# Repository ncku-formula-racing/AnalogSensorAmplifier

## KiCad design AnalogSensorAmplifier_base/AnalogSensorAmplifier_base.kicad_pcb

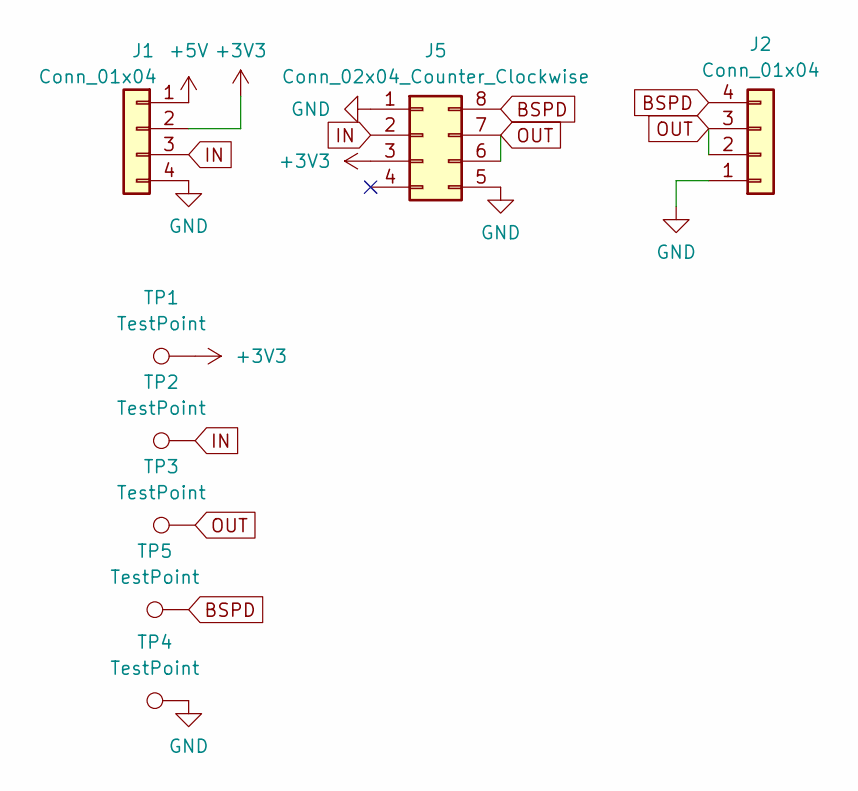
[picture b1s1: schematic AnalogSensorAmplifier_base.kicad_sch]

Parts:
J1, J2: Conn_01x04; PinHeader_1x04_P2.54mm_Vertical
J5: Conn_02x04_Counter_Clockwise; AnalogSensorAmplifier
TP1, TP2, TP3, TP4, TP5: TestPoint; TestPoint_THTPad_D1.0mm_Drill0.5mm

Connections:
+3V3: J1.2, J5.3, TP1.1
+5V: J1.1
BSPD: J2.4, J5.8, TP5.1
GND: J1.4, J2.1, J5.1, J5.5, TP4.1
IN: J1.3, J5.2, TP2.1
OUT: J2.2, J2.3, J5.6, J5.7, TP3.1

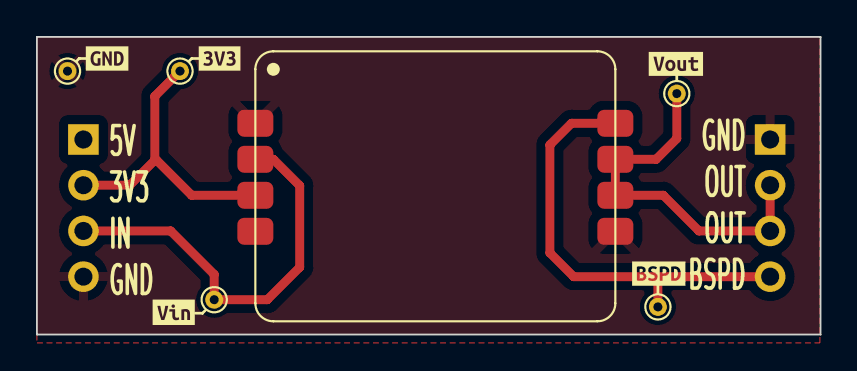
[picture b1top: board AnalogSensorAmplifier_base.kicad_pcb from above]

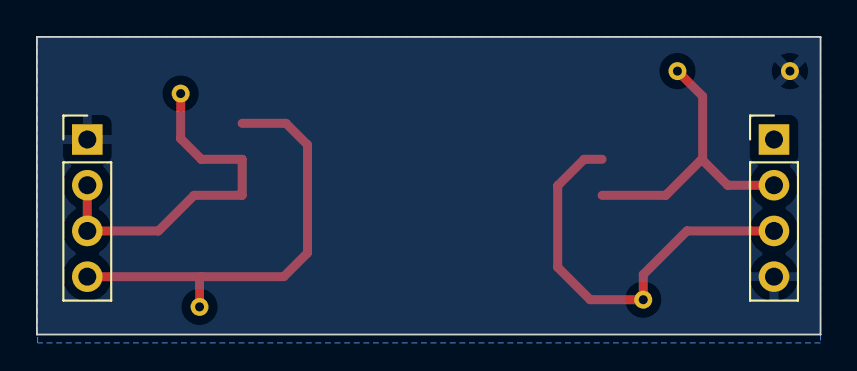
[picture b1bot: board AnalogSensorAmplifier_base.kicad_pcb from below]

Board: 2 copper layers, 43.5 x 16.5 mm, 13 parts (2 on the bottom side), 5 nets.

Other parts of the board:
kibuzzard-6607C7C2: G***; kibuzzard-6607C7C2
kibuzzard-6607C7E7: G***; kibuzzard-6607C7E7
kibuzzard-6607C702: G***; kibuzzard-6607C702
kibuzzard-6607C735: G***; kibuzzard-6607C735
kibuzzard-6607C802: G***; kibuzzard-6607C802

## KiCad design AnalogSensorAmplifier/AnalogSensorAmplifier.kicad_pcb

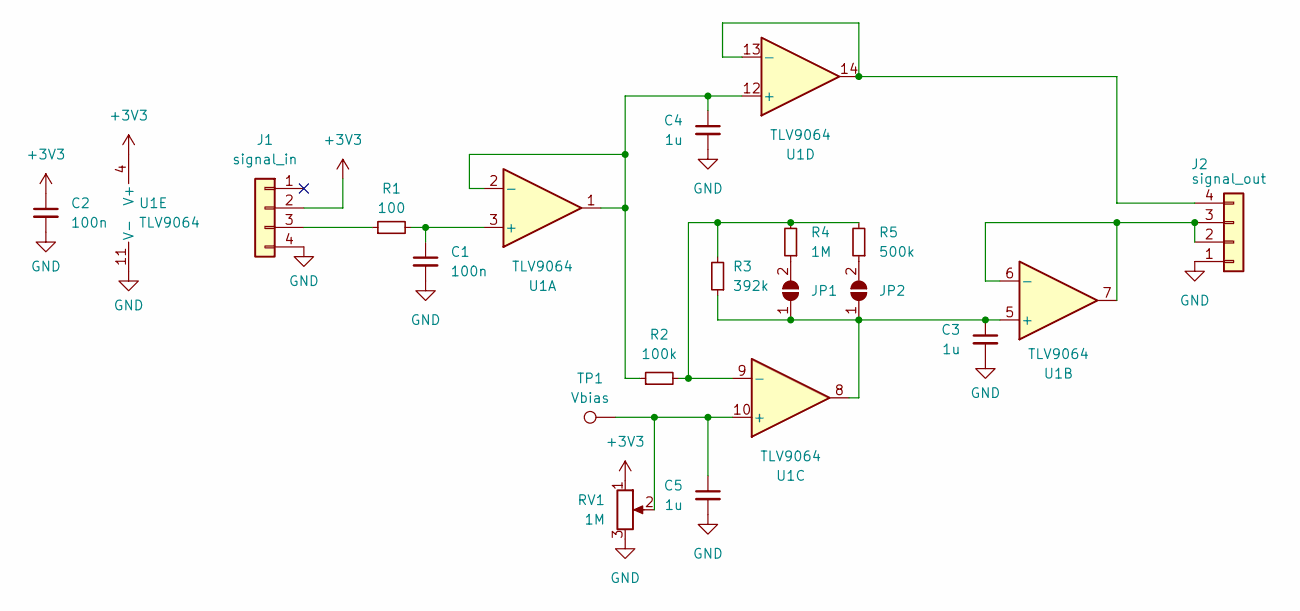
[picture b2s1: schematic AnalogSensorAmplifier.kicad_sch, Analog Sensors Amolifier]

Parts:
C1, C2: 100n; C_0603_1608Metric
C3, C4, C5: 1u; C_0603_1608Metric
J1: signal_in; PinHeader_1x04_P2.00mm_Vertical
J2: signal_out; PinHeader_1x04_P2.00mm_Vertical
JP1, JP2: SolderJumper_2_Open; small jumper
R1: 100; R_0603_1608Metric
R2: 100k; R_0603_1608Metric
R3: 392k; R_0603_1608Metric
R4: 1M; R_0603_1608Metric
R5: 500k; R_0603_1608Metric
RV1: 1M; PVG3A
TP1: Vbias; TestPoint_THTPad_D1.0mm_Drill0.5mm
U1: TLV9064; SOIC-14_3.9x8.7mm_P1.27mm

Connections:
+3V3: C2.1, J1.2, RV1.1, U1.4 (V+)
GND: C1.2, C2.2, C3.2, C4.2, C5.2, J1.4, J2.1, RV1.3, U1.11 (V-)
unnamed: J1.3, R1.1
unnamed: J2.2, J2.3, U1.6 (-), U1.7
unnamed: J2.4, U1.13 (-), U1.14
unnamed: C3.1, JP1.1 (A), JP2.1 (A), R3.1, U1.5 (+), U1.8
unnamed: JP1.2 (B), R4.1
unnamed: JP2.2 (B), R5.1
unnamed: C1.1, R1.2, U1.3 (+)
unnamed: C4.1, R2.1, U1.1, U1.2 (-), U1.12 (+)
unnamed: C5.1, RV1.2, TP1.1, U1.10 (+)
unnamed: R2.2, R3.2, R4.2, R5.2, U1.9 (-)

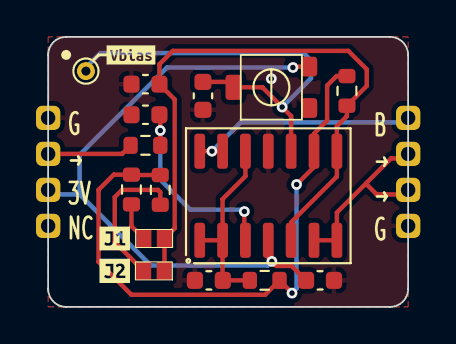
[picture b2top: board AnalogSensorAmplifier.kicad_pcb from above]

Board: 2 copper layers, 20.0 x 15.0 mm, 20 parts (0 on the bottom side), 12 nets.

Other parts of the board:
kibuzzard-6607A514: G***; kibuzzard-6607A514
kibuzzard-6607B0F2: G***; kibuzzard-6607B0F2
kibuzzard-6607203A: G***; kibuzzard-6607203A

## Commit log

2024-03-30 Upload PCB source files
2024-03-30 Add output path
2024-03-30 Add BOM csv
